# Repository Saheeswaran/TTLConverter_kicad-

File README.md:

View this project on [CADLAB.io](https://cadlab.io/project/30485). 

# TTLConverter_kicad-

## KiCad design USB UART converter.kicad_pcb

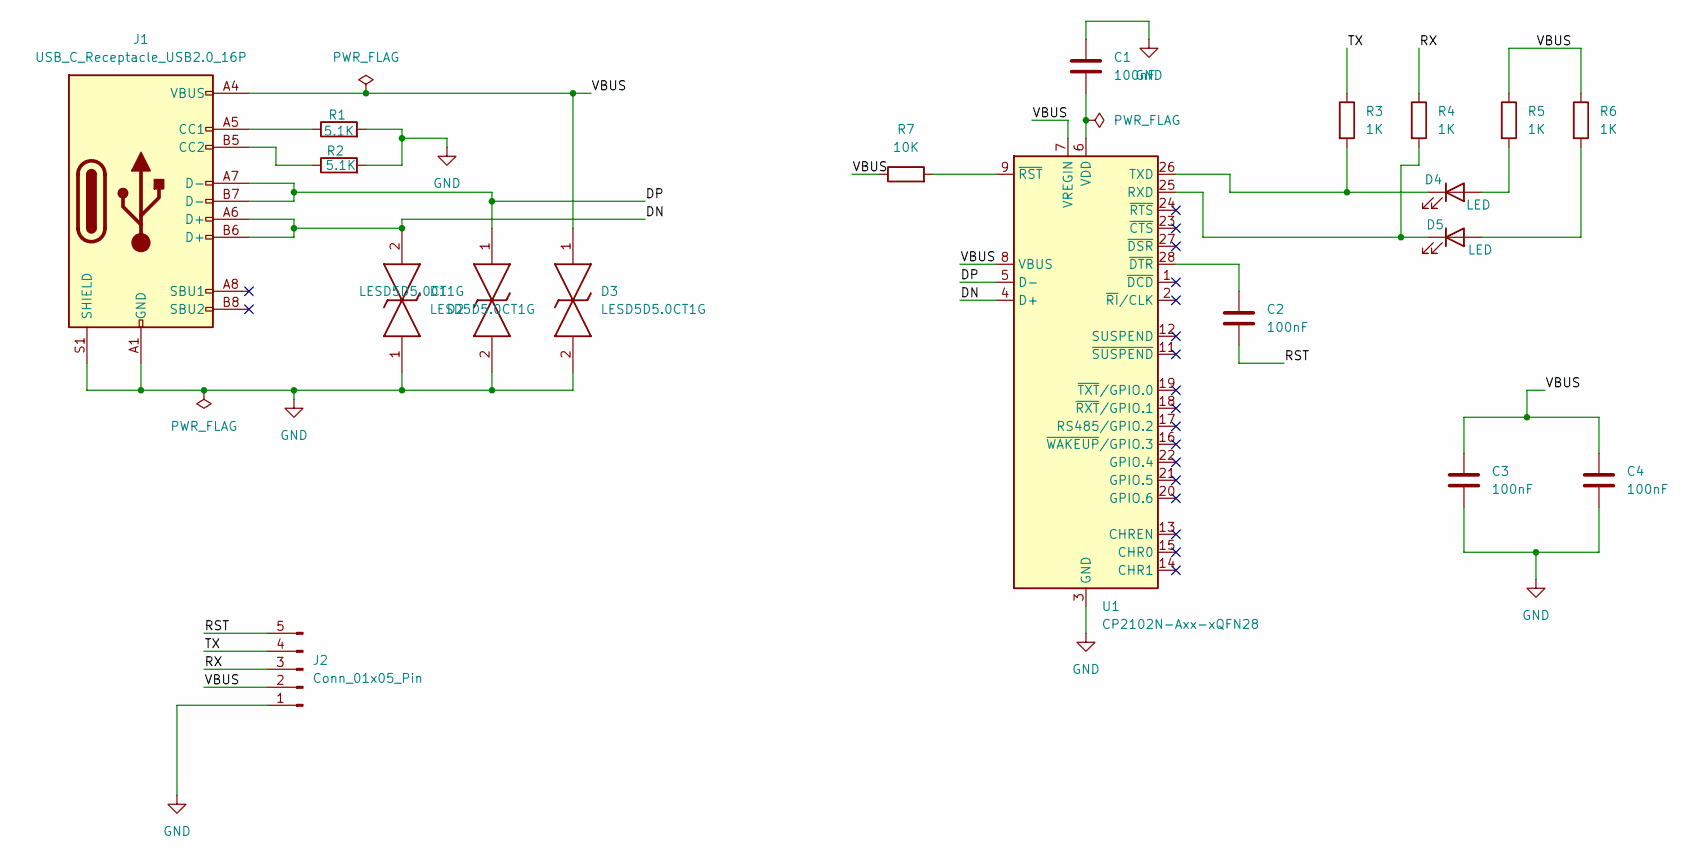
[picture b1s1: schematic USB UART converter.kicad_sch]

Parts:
C1, C2, C3, C4: 100nF; C_0201_0603Metric
D1, D2, D3: LESD5D5.0CT1G; LESD5D50CT1G; Manufacturer_Part_Number LESD5D5.0CT1G
D4, D5: LED; LED_0201_0603Metric
J1: USB_C_Receptacle_USB2.0_16P; USB_C_Receptacle_HRO_TYPE-C-31-M-12
J2: Conn_01x05_Pin; PinHeader_1x05_P2.54mm_Horizontal
R1, R2: 5.1K; R_0201_0603Metric
R3, R4, R5, R6: 1K; R_0201_0603Metric
R7: 10K; R_0201_0603Metric
U1: CP2102N-Axx-xQFN28; QFN-28-1EP_5x5mm_P0.5mm_EP3.35x3.35mm

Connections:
/DN: D1.2, J1.A6 (D+), J1.B6 (D+), U1.4 (D+)
/DP: D2.1, J1.A7 (D-), J1.B7 (D-), U1.5 (D-)
/RST: C2.2, J2.5
/RX: J2.3, R4.1
/TX: J2.4, R3.1
/VBUS: C3.1, C4.1, D3.1, J1.A4 (VBUS), J1.A9 (VBUS), J1.B4 (VBUS), J1.B9 (VBUS), J2.2, R5.1, R6.1, R7.1, U1.7 (VREGIN), U1.8 (VBUS)
GND: C1.1, C3.2, C4.2, D1.1, D2.2, D3.2, J1.A1 (GND), J1.A12 (GND), J1.B1 (GND), J1.B12 (GND), J1.S1 (SHIELD), J2.1, R1.2, R2.2, U1.3 (GND), U1.29 (GND)
unnamed: D4.2 (A), R5.2
unnamed: D4.1 (K), R3.2, U1.26 (TXD)
unnamed: D5.2 (A), R6.2
unnamed: D5.1 (K), R4.2, U1.25 (RXD)
unnamed: J1.A5 (CC1), R1.1
unnamed: J1.B5 (CC2), R2.1
unnamed: C1.2, U1.6 (VDD)
unnamed: C2.1, U1.28 (~DTR)
unnamed: R7.2, U1.9 (~RST)

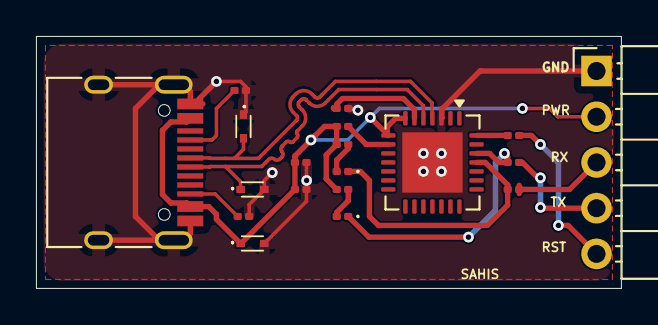
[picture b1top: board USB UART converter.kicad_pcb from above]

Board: 2 copper layers, 32.5 x 14.0 mm, 19 parts (0 on the bottom side), 16 nets.
